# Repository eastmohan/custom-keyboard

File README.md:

# custom-keyboard
**What?** </br>
This is a custom keyboard using KB2040 board. It has 63 keys and a 0.91" OLED. See below for the key assignments. 

**Why?** </br>
I am making this because I prefer using a keyboard to work at home rather than the one built in to my computer. The only keyboard I have is an old, somewhat broken membrane keyboard so I figured I'd try to make a custom mechanical one. I previously made a custom macropad, so I thought this would be a cool next step.

NOTE: You may have noticed that there is no .f3d file in the CAD folder. Instead, there is a .f3z file. They are the same except Fusion360, which I used for the CAD, only gives the option to save as .f3z (not .f3d) when you reference other components. Those referenced components are also included in the CAD folder in the **Premade Files** folder.

**To build this project:**
- Upload gerber and drill files to PCB manufacturer website
- Order PCB and components in the BOM
- Place the switches in the PCB
- **Switches should be placed through the keyboard lid 3D print to the PCB**
- Solder switches
- Place the diodes in the PCB in the correct orientation
- Solder the diodes
- Place the microcontroller
- Solder the microcontroller pin headers to the PCB and to the microcontroller
- Place button and solder
- 3D print case and insert PCB
- Plug microcontroller into computer in boot mode, upload firmware
- Enjoy your new keyboard!

**Schematic**

**PCB**

**Case CAD**

**Key Assignments**
 <br>
**BOM**
|Part|Source|Quantity|Cost Each|Total Cost|Link|
|---|---|---|---|---|---|
|Keycaps (Mecha Blue)|AliExpress|1|$9.38|$9.38|[Link](https://www.aliexpress.us/item/3256806811144120.html?spm=a2g0o.order_list.order_list_main.15.67dd1802SqQ127&gatewayAdapt=glo2usa)|
|Gateron Milky Yellow Pro 2 Switches|Amazon|1|$16.99|$16.99|[Link](https://www.amazon.com/dp/B0C2CWR4HH)|
|KB2040 Microcontroller|Adafruit|1|$8.95|$8.95|[Link](https://www.adafruit.com/product/5302)|
|USBC to USBA Cable|Amazon|1|$7.99|$7.99|[Link](https://www.amazon.com/Braided-Charging-iPhone-Samsung-Galaxy/dp/B0DPMQ7291/ref=sr_1_4?crid=1SV9OQJ048SWS&dib=eyJ2IjoiMSJ9.1t_2XikISDzveg5nagPE0osNztl9bqwsHxHaHrGNq6hm7c9BJ_g8DJaeP1sEOdZtq3GrKx_aNwRnCAJOK7a4xJjF3GMVWhFA84iwxPCt5IJeXU6zeOU8oJurPdHROuHPUsCsTca_lrhLE9L4tWy0N4hVSOnbrXtH1Ri7jv9zJy1u3zTaOMaxk9RhAfsR8RmF5K1eOlQCSqZNy2EQK8HV9HiO4tE7u-m53guYARivf1k.ZMKklFA6W2eYaHiiWo_QT39ANmk60e5_CI-Pl7Umad4&dib_tag=se&keywords=usbc%2Busb%2Bcable%2B2%2Bfeet&qid=1779670729&sprefix=usbc%2Busba%2Bcable%2B2%2Bfe%2Caps%2C183&sr=8-4&th=1)|
|Diodes|Aliexpress|1|$12.53|$12.53|[Link](https://www.aliexpress.us/item/3256807937287294.html?spm=a2g0o.productlist.main.10.4a48236dlb1ulY&algo_pvid=7bcbbf45-a950-43e8-8da5-f85b5c0ce52b&algo_exp_id=7bcbbf45-a950-43e8-8da5-f85b5c0ce52b-9&pdp_ext_f=%7B%22order%22%3A%2228%22%2C%22eval%22%3A%221%22%2C%22fromPage%22%3A%22search%22%7D&pdp_npi=6%40dis%21USD%2112.53%216.26%21%21%2184.81%2142.40%21%402103128917796710031653240e40c9%2112000043887291867%21sea%21US%217284814403%21X%211%210%21n_tag%3A-29919%3Bd%3A65aee796%3Bm03_new_user%3A-29895&curPageLogUid=lxjO2qs5uYjp&utparam-url=scene%3Asearch%7Cquery_from%3A%7Cx_object_id%3A1005008123602046%7C_p_origin_prod%3A)|
|0.91" OLED|Aliexpress|1|$2.89|$2.89|[Link](https://www.aliexpress.us/item/3256808615612857.html?spm=a2g0o.productlist.main.1.5f15WDCOWDCO9U&algo_pvid=a1ccd8df-943e-468a-b3d0-372a8e1068db&algo_exp_id=a1ccd8df-943e-468a-b3d0-372a8e1068db-0&pdp_ext_f=%7B%22order%22%3A%2275%22%2C%22eval%22%3A%221%22%2C%22fromPage%22%3A%22search%22%7D&pdp_npi=6%40dis%21USD%212.89%212.89%21%21%2119.54%2119.54%21%40210311cc17796710867325070ef3b7%2112000046723121361%21sea%21US%217284814403%21X%211%210%21n_tag%3A-29919%3Bd%3A65aee796%3Bm03_new_user%3A-29895&curPageLogUid=SMtCSefS9n5l&utparam-url=scene%3Asearch%7Cquery_from%3A%7Cx_object_id%3A1005008801927609%7C_p_origin_prod%3A)|
|M3 Heatset Insert, OD 4.2mm|Aliexpress|1|$3.60|$3.60|[Link](https://www.aliexpress.us/item/3256803396040989.html?spm=a2g0o.productlist.main.1.12841c1fxjyqbd&algo_pvid=59fb9b6a-9e77-4cc9-a433-e1661f4e88bf&algo_exp_id=59fb9b6a-9e77-4cc9-a433-e1661f4e88bf-0&pdp_ext_f=%7B%22order%22%3A%2266511%22%2C%22eval%22%3A%221%22%2C%22fromPage%22%3A%22search%22%7D&pdp_npi=6%40dis%21USD%212.22%210.99%21%21%2115.02%216.70%21%402101e80317796711398037554ee987%2112000026370649739%21sea%21US%217284814403%21X%211%210%21n_tag%3A-29919%3Bd%3A65aee796%3Bm03_new_user%3A-29895%3BpisId%3A5000000205925297&curPageLogUid=5DKc8jmBy4oP&utparam-url=scene%3Asearch%7Cquery_from%3A%7Cx_object_id%3A1005003582355741%7C_p_origin_prod%3A)|
|Stabilizers|Aliexpress|1|$5.92|$5.92|[Link](https://www.aliexpress.us/item/3256801499984864.html?spm=a2g0o.productlist.main.2.7da2zb90zb90Le&algo_pvid=30dd5091-d972-4682-929c-91c60e420566&algo_exp_id=30dd5091-d972-4682-929c-91c60e420566-1&pdp_ext_f=%7B%22order%22%3A%22291%22%2C%22eval%22%3A%221%22%2C%22fromPage%22%3A%22search%22%7D&pdp_npi=6%40dis%21USD%215.92%213.22%21%21%215.92%213.22%21%402103129017796716912624545e465f%2112000017133740377%21sea%21US%217284814403%21X%211%210%21n_tag%3A-29919%3Bd%3A65aee796%3Bm03_new_user%3A-29895%3BpisId%3A5000000204411062&curPageLogUid=MbHZPmZU1SUn&utparam-url=scene%3Asearch%7Cquery_from%3A%7Cx_object_id%3A1005001686299616%7C_p_origin_prod%3A)|
|PCB|JLCPCB|1 (5 pack)|$17.10|$17.10|Use production files in the PCB folder of this repository.|

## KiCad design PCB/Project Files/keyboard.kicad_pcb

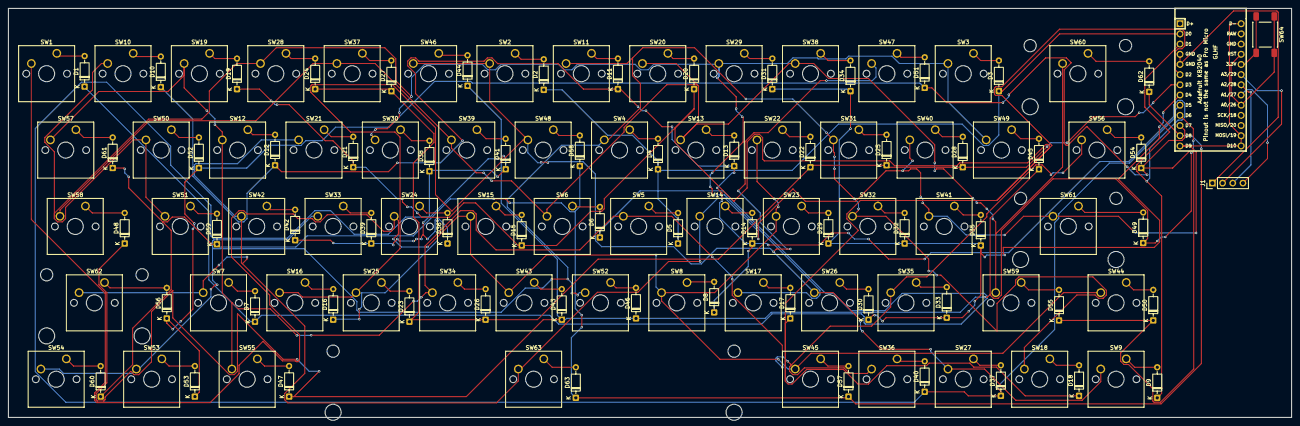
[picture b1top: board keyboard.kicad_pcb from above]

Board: 2 copper layers, 320.0 x 102.0 mm, 129 parts (0 on the bottom side), 85 nets.

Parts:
D1, D2, D3, D4, D5, D6, D7, D8, D9, D10, D11, D12, D13, D14, D15, D16, D17, D18, D19, D20, D21, D22, D23, D24, D25, D26, D27, D28, D29, D30, D31, D32, D33, D34, D35, D36, D37, D38, D39, D40, D41, D42, D43, D44, D45, D46, D47, D48, D49, D50, D51, D52, D53, D54, D55, D56, D57, D58, D59, D60, D61, D62, D63: 1N4148; D_DO-35_SOD27_P7.62mm_Horizontal
J1: Conn_01x04; PinHeader_1x04_P2.54mm_Vertical
SW1, SW2, SW3, SW4, SW5, SW6, SW7, SW8, SW9, SW10, SW11, SW12, SW13, SW14, SW15, SW16, SW17, SW18, SW19, SW20, SW21, SW22, SW23, SW24, SW25, SW26, SW27, SW28, SW29, SW30, SW31, SW32, SW33, SW34, SW35, SW36, SW37, SW38, SW39, SW40, SW41, SW42, SW43, SW44, SW45, SW46, SW47, SW48, SW49, SW50, SW51, SW52: SW_Push; SW_Cherry_MX_1.00u_PCB
SW53, SW54, SW55: SW_Push; SW_Cherry_MX_1.25u_PCB
SW56, SW57: SW_Push; SW_Cherry_MX_1.50u_PCB
SW58, SW59: SW_Push; SW_Cherry_MX_1.75u_PCB
SW60: SW_Push; SW_Cherry_MX_2.00u_PCB
SW61, SW62: SW_Push; SW_Cherry_MX_2.25u_PCB
SW63: SW_Push; SW_Cherry_MX_6.25u_PCB
SW64: SW_Push; SW_Push_1P1T_NO_E-Switch_TL3301NxxxxxG
U1: kb2040

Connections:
/COL0: SW7.2, SW14.2, SW21.2, SW40.2, SW41.2, SW42.2, SW61.2, SW62.2, SW63.2, U1.13 (D9)
/COL1: SW6.2, SW13.2, SW20.2, SW37.2, SW38.2, SW39.2, SW58.2, SW59.2, SW60.2
/COL2: SW5.2, SW12.2, SW19.2, SW34.2, SW35.2, SW36.2, SW55.2, SW56.2, SW57.2
/COL3: SW4.2, SW11.2, SW18.2, SW31.2, SW32.2, SW33.2, SW52.2, SW53.2, SW54.2
/COL4: SW3.2, SW10.2, SW17.2, SW28.2, SW29.2, SW30.2, SW49.2, SW50.2, SW51.2
/COL5: SW2.2, SW9.2, SW16.2, SW25.2, SW26.2, SW27.2, SW46.2, SW47.2, SW48.2
/COL6: SW1.2, SW8.2, SW15.2, SW22.2, SW23.2, SW24.2, SW43.2, SW44.2, SW45.2
/ROW0: D1.1 (K), D2.1 (K), D3.1 (K), D4.1 (K), D5.1 (K), D6.1 (K), D7.1 (K), U1.2 (D0)
/ROW1: D8.1 (K), D9.1 (K), D10.1 (K), D11.1 (K), D12.1 (K), D13.1 (K), D14.1 (K), U1.3 (D1)
/ROW2: D15.1 (K), D16.1 (K), D17.1 (K), D18.1 (K), D19.1 (K), D20.1 (K), D21.1 (K), U1.6 (D2)
/ROW3: D22.1 (K), D23.1 (K), D24.1 (K), D25.1 (K), D26.1 (K), D27.1 (K), D28.1 (K), U1.7 (D3)
/ROW4: D29.1 (K), D30.1 (K), D31.1 (K), D32.1 (K), D33.1 (K), D34.1 (K), D35.1 (K), U1.8 (D4)
/ROW5: D36.1 (K), D37.1 (K), D38.1 (K), D39.1 (K), D40.1 (K), D41.1 (K), D42.1 (K), U1.9 (D5)
/ROW6: D43.1 (K), D44.1 (K), D45.1 (K), D46.1 (K), D47.1 (K), D48.1 (K), D49.1 (K), U1.10 (D6)
/ROW7: D50.1 (K), D51.1 (K), D52.1 (K), D53.1 (K), D54.1 (K), D55.1 (K), D56.1 (K), U1.11 (D7)
/ROW8: D57.1 (K), D58.1 (K), D59.1 (K), D60.1 (K), D61.1 (K), D62.1 (K), D63.1 (K), U1.12 (D8)
/SCL: J1.3, U1.19 (A3/29)
/SDA: J1.4, U1.20 (A2/28)
/VCC: J1.2, U1.18 (3.3v)
GND: J1.1, U1.4 (GND), U1.5 (GND)
unnamed: D1.2 (A), SW1.1
unnamed: D2.2 (A), SW2.1
unnamed: D3.2 (A), SW3.1
unnamed: D4.2 (A), SW4.1
unnamed: D5.2 (A), SW5.1
unnamed: D6.2 (A), SW6.1
unnamed: D7.2 (A), SW7.1
unnamed: D8.2 (A), SW8.1
unnamed: D9.2 (A), SW9.1
unnamed: D10.2 (A), SW10.1
unnamed: D11.2 (A), SW11.1
unnamed: D12.2 (A), SW12.1
unnamed: D13.2 (A), SW13.1
unnamed: D14.2 (A), SW14.1
unnamed: D15.2 (A), SW15.1
unnamed: D16.2 (A), SW16.1
unnamed: D17.2 (A), SW17.1
unnamed: D18.2 (A), SW18.1
unnamed: D19.2 (A), SW19.1
unnamed: D20.2 (A), SW20.1
unnamed: D21.2 (A), SW21.1
unnamed: D22.2 (A), SW22.1
unnamed: D23.2 (A), SW25.1
unnamed: D24.2 (A), SW28.1
unnamed: D25.2 (A), SW31.1
unnamed: D26.2 (A), SW34.1
unnamed: D27.2 (A), SW37.1
unnamed: D28.2 (A), SW40.1
unnamed: D29.2 (A), SW23.1
unnamed: D30.2 (A), SW26.1
unnamed: D31.2 (A), SW29.1
unnamed: D32.2 (A), SW32.1
unnamed: D33.2 (A), SW35.1
unnamed: D34.2 (A), SW38.1
unnamed: D35.2 (A), SW41.1
unnamed: D36.2 (A), SW24.1
unnamed: D37.2 (A), SW27.1
unnamed: D38.2 (A), SW30.1
unnamed: D39.2 (A), SW33.1
unnamed: D40.2 (A), SW36.1
unnamed: D41.2 (A), SW39.1
unnamed: D42.2 (A), SW42.1
unnamed: D43.2 (A), SW43.1
unnamed: D44.2 (A), SW46.1
unnamed: D45.2 (A), SW49.1
unnamed: D46.2 (A), SW52.1
unnamed: D47.2 (A), SW55.1
unnamed: D48.2 (A), SW58.1
unnamed: D49.2 (A), SW61.1
unnamed: D50.2 (A), SW44.1
unnamed: D51.2 (A), SW47.1
unnamed: D52.2 (A), SW50.1
unnamed: D53.2 (A), SW53.1
unnamed: D54.2 (A), SW56.1
unnamed: D55.2 (A), SW59.1
unnamed: D56.2 (A), SW62.1
unnamed: D57.2 (A), SW45.1
unnamed: D58.2 (A), SW48.1
unnamed: D59.2 (A), SW51.1
unnamed: D60.2 (A), SW54.1
unnamed: D61.2 (A), SW57.1
unnamed: D62.2 (A), SW60.1
unnamed: D63.2 (A), SW63.1
unnamed: SW64.1, U1.16 (GND)
unnamed: SW64.2, U1.17 (RESET)

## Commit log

2026-05-25 PCB Files
2026-05-25 CAD and PCB Files
2026-05-25 Added CAD and PCB Files
2026-05-26 Added case CAD
2026-05-26 Updated CAD to reflect new PCB version
2026-05-26 Rename custom-keyboard-journal-5-25-2026.md to JOURNAL.md
2026-05-26 Added BOM .csv
2026-05-26 Added PCB Production Files
2026-05-27 Add Key Assignments
2026-05-28 Wrote firmware
2026-05-28 Updated CAD
2026-05-28 moved the PDF
2026-05-28 Move BOM
